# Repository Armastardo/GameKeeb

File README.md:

# GameKeeb
PCB for a Keyboard to GC adapter

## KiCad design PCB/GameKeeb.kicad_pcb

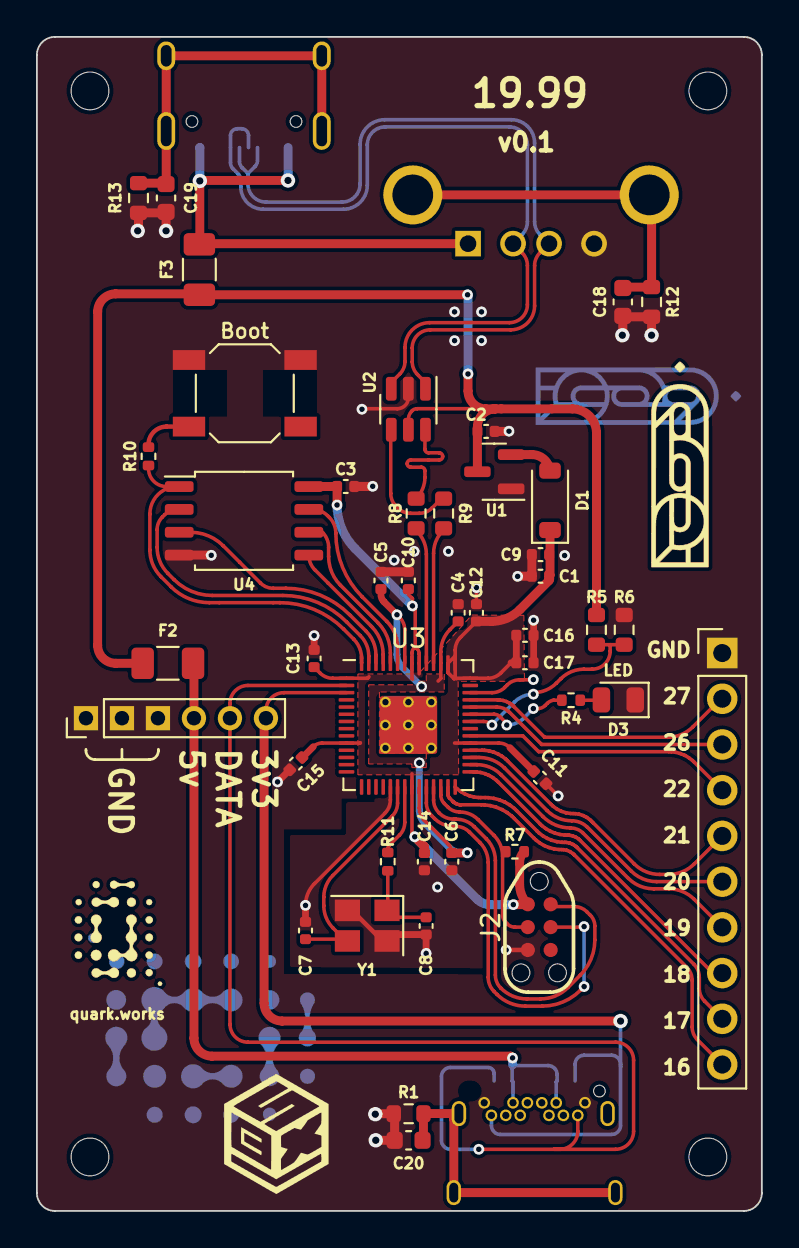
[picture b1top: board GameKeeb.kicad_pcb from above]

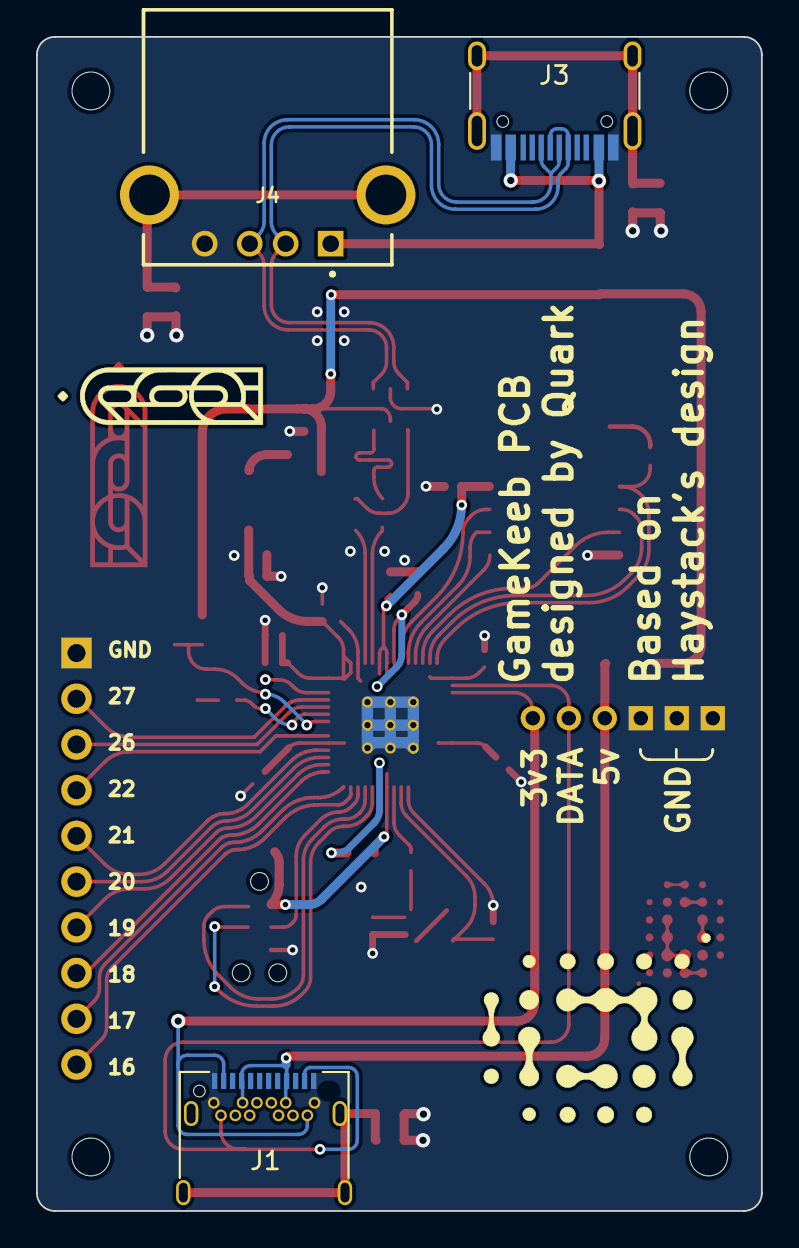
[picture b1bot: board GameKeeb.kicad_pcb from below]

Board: 2 copper layers, 40.3 x 65.2 mm, 55 parts (5 on the bottom side), 43 nets.

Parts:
C1, C2, C4, C10: 1uF; C_0402_1005Metric
C3, C5, C6, C11, C12, C13, C14, C15, C16, C17: 100nF; C_0402_1005Metric
C7, C8: 22pF; C_0402_1005Metric
C9: 10uF; C_0402_1005Metric
C18, C19, C20: 4.7uF; C_0603_1608Metric
D1: Schottky Diode; D_SOD-123
D3: LED; LED_0805_2012Metric
F2, F3: 500 mA; Fuse_1206_3216Metric
H1, H2, H3, H4: MountingHole; MountingHole_2.1mm
H5: qw logo; qw new logo silk + copper sm
H6, H8: 1999 logo; 1999 logo md
H7: qw logo; qw new logo silk + copper md
J1: USB C Connector; TYPE-C_24P_QCHT
J2: JTAG_TC2030; CON_TC2030_outlined
J3: USB_C_Receptacle_USB2.0; USB_C_Receptacle_HRO_TYPE-C-31-M-12
J4: USB_A; GCT_USB1130-15-A_REVA
J5: GCC Cable; PinHeader_1x06_P2.00mm_Vertical
J6: Conn_01x10_Pin; PinHeader_1x10_P2.54mm_Vertical
R1, R12, R13: 1M; R_0603_1608Metric
R4: 470; R_0402_1005Metric
R5: 5.6k; R_0603_1608Metric
R6: 10k; R_0603_1608Metric
R7: 10k; R_0402_1005Metric
R8, R9: 27; R_0603_1608Metric
R10, R11: 1k; R_0402_1005Metric
SW1: Boot; SW_SPST_SKQG_WithStem
U1: XC6206; SOT-23
U2: USBLC6-2SC6; SOT-23-6
U3: RP2040; RP2040-QFN-56
U4: W25Q128JVS; SOIC-8_5.23x5.23mm_P1.27mm
Y1: 12MHz; Crystal_SMD_3225-4Pin_3.2x2.5mm

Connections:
3vCable: J1.A2 (TX1+), J1.B2 (TX2+), J5.6, U3.3 (GPIO1)
+1V1: C4.1, C5.1, C6.1, U3.23 (DVDD), U3.45 (VREG_VOUT), U3.50 (DVDD)
+3V3: C1.2, C3.1, C9.1, C10.1, C11.1, C12.1, C13.1, C14.1, C15.1, C16.1, C17.1, D1.1 (K), J2.1 (VCC), R7.1, U3.1 (IOVDD), U3.10 (IOVDD), U3.22 (IOVDD), U3.33 (IOVDD), U3.42 (IOVDD), U3.43 (ADC_AVDD), U3.44 (VREG_VIN), U3.48 (USB_VDD), U3.49 (IOVDD), U4.8 (VCC)
+5V: C2.2, F2.1, F3.1, R5.1, U1.3 (VI), U2.5 (VBUS)
/D_+: R8.2, U3.47 (D+)
/D_-: R9.2, U3.46 (D-)
/XTAL_O: C8.2, R11.1, Y1.1
/~USB_BOOT: R10.1, SW1.2
CS: R10.2, U3.56 (QSPI_SS_N), U4.1 (~CS)
D+: R8.1, U2.6 (I/O1)
D-: R9.1, U2.4 (I/O2)
DATA: J1.A11 (RX2+), J1.B11 (RX1+), J5.5, U3.2 (GPIO0)
DBUS+: J3.A6 (D+), J3.B6 (D+), J4.3 (D+), U2.1 (I/O1)
DBUS-: J3.A7 (D-), J3.B7 (D-), J4.2 (D-), U2.3 (I/O2)
GCC 5v: F2.2, J1.A4 (VBUS), J1.A9 (VBUS), J1.B4 (VBUS), J1.B9 (VBUS), J5.4
GND: C1.1, C2.1, C3.2, C4.2, C5.2, C6.2, C7.1, C8.1, C9.2, C10.2, C11.2, C12.2, C13.2, C14.2, C15.2, C16.2, C17.2, C18.2, C19.2, C20.1, D3.1 (K), J1.A1 (GND), J1.A12 (GND), J1.B1 (GND), J1.B12 (GND), J2.5 (GND), J3.A1 (GND), J3.A12 (GND), J3.B1 (GND), J3.B12 (GND), J4.4 (GND), J5.1, J5.2, J5.3, J6.1, R1.1, R6.2, R12.1, R13.1, SW1.1, U1.1 (GND), U2.2 (GND), U3.19 (TESTEN), U3.57 (GND), U4.4 (GND), Y1.2, Y1.4
GP16: J6.10, U3.27 (GPIO16)
GP17: J6.9, U3.28 (GPIO17)
GP18: J6.8, U3.29 (GPIO18)
GP19: J6.7, U3.30 (GPIO19)
GP20: J6.6, U3.31 (GPIO20)
GP21: J6.5, U3.32 (GPIO21)
GP22: J6.4, U3.34 (GPIO22)
GP26: J6.3, U3.38 (GPIO26/ADC0)
GP27: J6.2, U3.39 (GPIO27/ADC1)
unnamed: D1.2 (A), U1.2 (VO)
unnamed: D3.2 (A), R4.2
unnamed: C20.2, J1.S1 (SHIELD), R1.2
unnamed: C19.1, J3.S1 (SHIELD), R13.2
unnamed: C18.1, J4.5 (Shield), R12.2
PICO_LED: R4.1, U3.37 (GPIO25)
QSPI_CLK: U3.52 (QSPI_SCLK), U4.6 (CLK)
SD0: U3.53 (QSPI_SD0), U4.5 (DI(IO0))
SD1: U3.55 (QSPI_SD1), U4.2 (DO(IO1))
SD2: U3.54 (QSPI_SD2), U4.3 (IO2)
SD3: U3.51 (QSPI_SD3), U4.7 (IO3)
SWCLK: J2.4 (SWCLK), U3.24 (SWCLK)
SWD: J2.2 (SWDIO), U3.25 (SWDIO)
VBUS: F3.2, J3.A4 (VBUS), J3.A9 (VBUS), J3.B4 (VBUS), J3.B9 (VBUS), J4.1 (VBUS)
VBUS_SENSE: R5.2, R6.1, U3.36 (GPIO24)
XTAL_IN: C7.2, U3.20 (XTAL_IN), Y1.3
XTAL_OUT: R11.2, U3.21 (XTAL_OUT)
~RESET: J2.3 (~RST), R7.2, U3.26 (~RUN)

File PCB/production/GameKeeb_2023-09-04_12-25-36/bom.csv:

Designator,Footprint,Quantity,Value,LCSC Part #
"C1, C10, C2, C4",0402,4,1uF,C52923
"C11, C12, C13, C14, C15, C16, C17, C3, C5, C6",0402,10,100nF,C1525
"C18, C19, C20",0603,3,4.7uF,
"C7, C8",0402,2,22pF,C1555
C9,0402,1,10uF,C15525
D1,D_SOD-123,1,Schottky Diode,C8598
D3,0805,1,LED,C2297
"F2, F3",1206,2,500 mA,C70076
"H1, H2, H3, H4",MountingHole_2.1mm,4,MountingHole,
H5,qw new logo silk + copper sm,1,qw logo,
"H6, H8",1999 logo md,2,1999 logo,
H7,qw new logo silk + copper md,1,qw logo,
J1,TYPE-C_24P_QCHT,1,USB C Connector,C456013
J2,CON_TC2030_outlined,1,JTAG_TC2030,
J3,USB_C_Receptacle_HRO_TYPE-C-31-M-12,1,USB_C_Receptacle_USB2.0,
J4,GCT_USB1130-15-A_REVA,1,USB_A,
J5,PinHeader_1x06_P2.00mm_Vertical,1,GCC Cable,
J6,PinHeader_1x10_P2.54mm_Vertical,1,Conn_01x10_Pin,
"R1, R12, R13",0603,3,1M,C25190
"R10, R11",0402,2,1k,C11702
R4,0402,1,470,C25744
R5,0603,1,5.6k,C23189
R6,0603,1,10k,C23192
R7,0402,1,10k,C25744
"R8, R9",0603,2,27,C25190
U1,SOT-23,1,XC6206,C5446
U2,SOT-23-6,1,USBLC6-2SC6,C7519
U3,RP2040-QFN-56,1,RP2040,C2040
U4,SOIC-8_5.23x5.23mm_P1.27mm,1,W25Q128JVS,C97521
Y1,Crystal_SMD_3225-4Pin_3.2x2.5mm,1,12MHz,C9002

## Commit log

2023-09-04 Initial revision
2023-09-04 Moved boot button a little to the top
